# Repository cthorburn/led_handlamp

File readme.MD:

# Dual-Channel LED Driver Module (3S Li-ion Powered)

An efficient, dual-channel constant-current LED driver system designed to run directly off a **3S Li-ion battery pack (9.0V – 12.6V)** without the need for intermediate buck converters. This design uses two independent **Texas Instruments TPS61165** boost regulator ICs to drive a bank of 15 white LEDs and a bank of 20 red LEDs with optimal efficiency and protection against thermal runaway.

---

## 🛠️ Circuit Architecture Overview

| Parameter | Channel 1: White LEDs | Channel 2: Red LEDs |
| :--- | :--- | :--- |
| **Driver IC** | **TPS61165** (Boost) | **TPS61165** (Boost) |
| **LED Count & Matrix** | 15 LEDs (3 Parallel × 5 Series) | 20 LEDs (2 Parallel × 10 Series) |
| **Per-LED Spec (Assumed)** | ~3.2V @ 20mA | ~2.0V @ 20mA |
| **Target Output Voltage (\(V_{OUT}\))** | **16.0 V** | **20.0 V** |
| **Target Output Current (\(I_{OUT}\))** | **60 mA** | **40 mA** |
| **Sense Resistor (\(R_{SET}\))** | **3.3 Ω** | **5.1 Ω** |

### Why This Topology?
* **No Linear Ballast Resistors:** Series strings inherently balance current natively within the branch, eliminating the need for 35 individual resistors and preventing thermal runaway domino failures.
* **Pure Boost Operation:** By structuring the red LEDs into strings of 10 (\(V_{OUT} = 20\text{V}\)), the target voltage stays safely above the maximum fully charged battery voltage (\(12.6\text{V}\)), allowing a common boost architecture for both channels.

---

## 📋 Bill of Materials (BOM) Per Channel

To build this system on your PCB, you will need to populate the following supporting components for **each** TPS61165 chip:

1. **IC₁ (LED Driver):** Texas Instruments TPS61165
2. **L₁ (Inductor):** `10 µH` to `22 µH` shielded power inductor. Saturation current (\(I_{SAT}\)) **must be \(\ge\) 1.5A**.
3. **D₁ (Schottky Diode):** Fast switching Schottky diode (e.g., **MBR0540** or **B140**). Must be rated for \(\ge\) 30V or 40V reverse breakdown voltage.
4. **C_{IN} (Input Capacitor):** `4.7 µF` to `10 µF` X7R Ceramic Capacitor (\(\ge\) 16V rated). Place immediately adjacent to the chip's power pins.
5. **C_{OUT} (Output Capacitor):** `1 µF` to `4.7 µF` X7R Ceramic Capacitor. **Crucial:** Must be rated for **\(\ge\) 35V or 50V** to handle the high-voltage boost output safely.
6. **C_{COMP} (Compensation):** `220 nF` Ceramic Capacitor connected from the `COMP` pin to Ground.
7. **R_{SET} (Current Sense Resistor):** 0603 or 0805 thick film surface mount resistor. 
   * *White Channel:* **3.3 Ω** (sets total output to 60mA)
   * *Red Channel:* **5.1 Ω** (sets total output to 40mA)

---

## 📐 PCB Layout & Routing Guidelines

The TPS61165 operates at a high switching frequency of **1.2 MHz**. Adhering strictly to these routing rules is necessary to prevent electromagnetic interference (EMI) and unexpected voltage ripple.

### Recommended Trace Widths (assuming 1 oz/ft² copper)
* **High-Current Power Input (Battery to Chip):** `0.6 mm to 1.0 mm` (24 to 40 mils). Applies to \(V_{IN}\) power rails running through the input decoupling capacitors, inductor, and IC power pin.
* **High-Frequency Switching Node:** `0.8 mm to 1.2 mm` (32 to 48 mils). Keep the node connecting the IC's `SW` pin, the inductor, and the Schottky diode **as short and wide as physically possible**. Do not route this trace near sensitive analog signals.
* **LED Output & Feedback Loop:** `0.25 mm to 0.4 mm` (10 to 16 mils). Safe for the 40mA–60mA smooth DC running out to the LED panels and returning back to the `FB` pin.

### Grounding & Component Placement
* Implement a continuous, unbroken **Ground Plane** on the bottom layer of the board.
* Connect the ground pads of \(C_{IN}\), \(C_{OUT}\), and \(R_{SET}\) straight down into the ground plane using short, fat traces or dedicated ground stitching vias.
* Place the loop consisting of the IC, Inductor, Diode, and Output Capacitor tightly clustered together. Keep the loop area minimized.

---

## 🎛️ Control & Dimming
Each driver can be turned on/off or dimmed independently using the `CTRL` pin. 
* **ON/OFF:** Pull `CTRL` High (\(\ge\) 1.2V) to enable, pull Low (\(\le\) 0.4V) to disable.
* **Dimming:** Apply a standard logic-level PWM signal from a microcontroller to the `CTRL` pin (acceptable frequency range: 5kHz to 100kHz).

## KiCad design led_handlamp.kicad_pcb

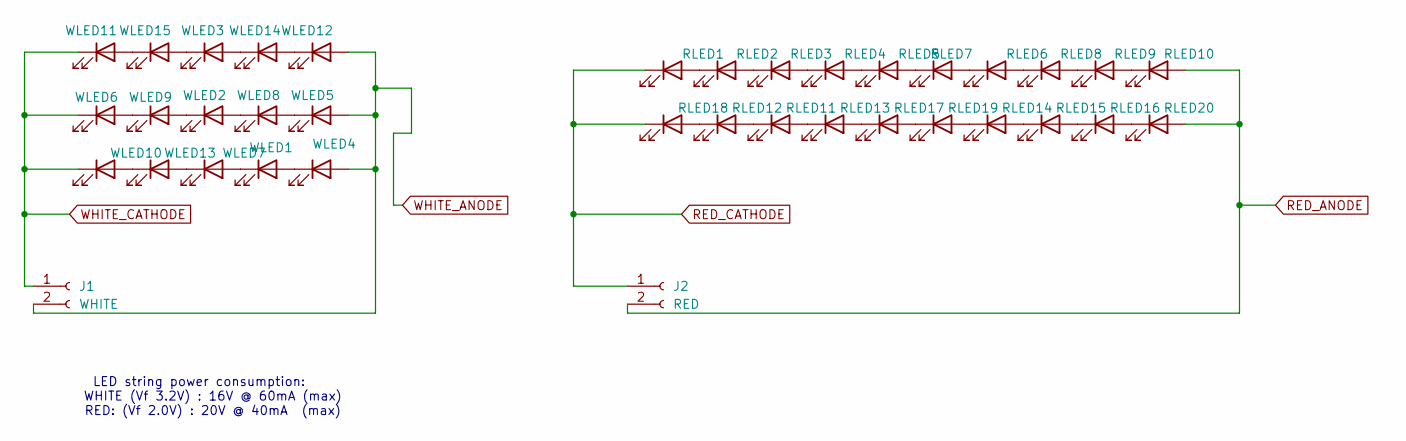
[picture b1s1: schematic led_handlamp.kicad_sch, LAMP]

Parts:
J1: WHITE; JST_XH_B2B-XH-A_1x02_P2.50mm_Vertical
J2: RED; JST_XH_B2B-XH-A_1x02_P2.50mm_Vertical
RLED1, RLED2, RLED3, RLED4, RLED5, RLED6, RLED7, RLED8, RLED9, RLED10, RLED11, RLED12, RLED13, RLED14, RLED15, RLED16, RLED17, RLED18, RLED19, RLED20: LED; LED_D5.0mm
WLED1, WLED2, WLED3, WLED4, WLED5, WLED6, WLED7, WLED8, WLED9, WLED10, WLED11, WLED12, WLED13, WLED14, WLED15: LED; LED_D5.0mm

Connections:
unnamed: RLED1.2 (A), RLED2.1 (K)
unnamed: RLED2.2 (A), RLED3.1 (K)
unnamed: RLED3.2 (A), RLED4.1 (K)
unnamed: RLED4.2 (A), RLED5.1 (K)
unnamed: RLED5.2 (A), RLED7.1 (K)
unnamed: RLED6.2 (A), RLED8.1 (K)
unnamed: RLED6.1 (K), RLED7.2 (A)
unnamed: RLED8.2 (A), RLED9.1 (K)
unnamed: RLED9.2 (A), RLED10.1 (K)
unnamed: RLED11.2 (A), RLED13.1 (K)
unnamed: RLED11.1 (K), RLED12.2 (A)
unnamed: RLED12.1 (K), RLED18.2 (A)
unnamed: RLED13.2 (A), RLED17.1 (K)
unnamed: RLED14.2 (A), RLED15.1 (K)
unnamed: RLED14.1 (K), RLED19.2 (A)
unnamed: RLED15.2 (A), RLED16.1 (K)
unnamed: RLED16.2 (A), RLED20.1 (K)
unnamed: RLED17.2 (A), RLED19.1 (K)
unnamed: WLED1.2 (A), WLED4.1 (K)
unnamed: WLED1.1 (K), WLED7.2 (A)
unnamed: WLED2.2 (A), WLED8.1 (K)
unnamed: WLED2.1 (K), WLED9.2 (A)
unnamed: WLED5.1 (K), WLED8.2 (A)
unnamed: WLED6.2 (A), WLED9.1 (K)
unnamed: WLED10.2 (A), WLED13.1 (K)
unnamed: WLED11.2 (A), WLED15.1 (K)
unnamed: WLED12.1 (K), WLED14.2 (A)
unnamed: WLED7.1 (K), WLED13.2 (A)
unnamed: WLED3.2 (A), WLED14.1 (K)
unnamed: WLED3.1 (K), WLED15.2 (A)
RED_ANODE: J2.2, RLED10.2 (A), RLED20.2 (A)
RED_CATHODE: J2.1, RLED1.1 (K), RLED18.1 (K)
WHITE_ANODE: J1.2, WLED4.2 (A), WLED5.2 (A), WLED12.2 (A)
WHITE_CATHODE: J1.1, WLED6.1 (K), WLED10.1 (K), WLED11.1 (K)

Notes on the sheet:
LED string power consumption: WHITE (Vf 3.2V) : 16V @ 60mA (max) RED: (Vf 2.0V) : 20V @ 40mA (max)

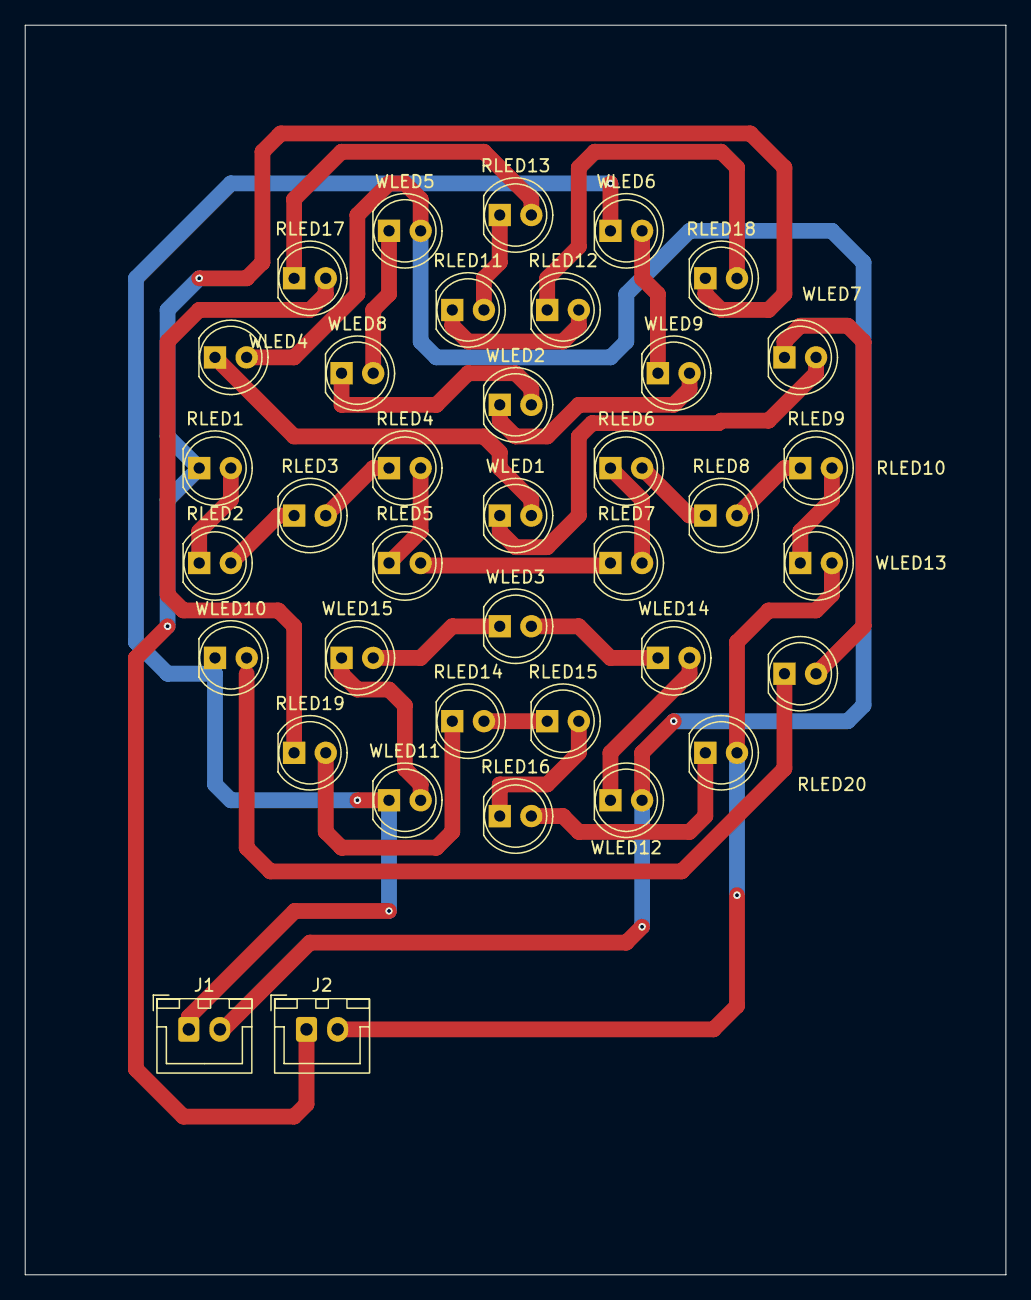
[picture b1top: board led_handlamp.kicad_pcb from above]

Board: 2 copper layers, 78.7 x 100.3 mm, 37 parts (0 on the bottom side), 34 nets.
